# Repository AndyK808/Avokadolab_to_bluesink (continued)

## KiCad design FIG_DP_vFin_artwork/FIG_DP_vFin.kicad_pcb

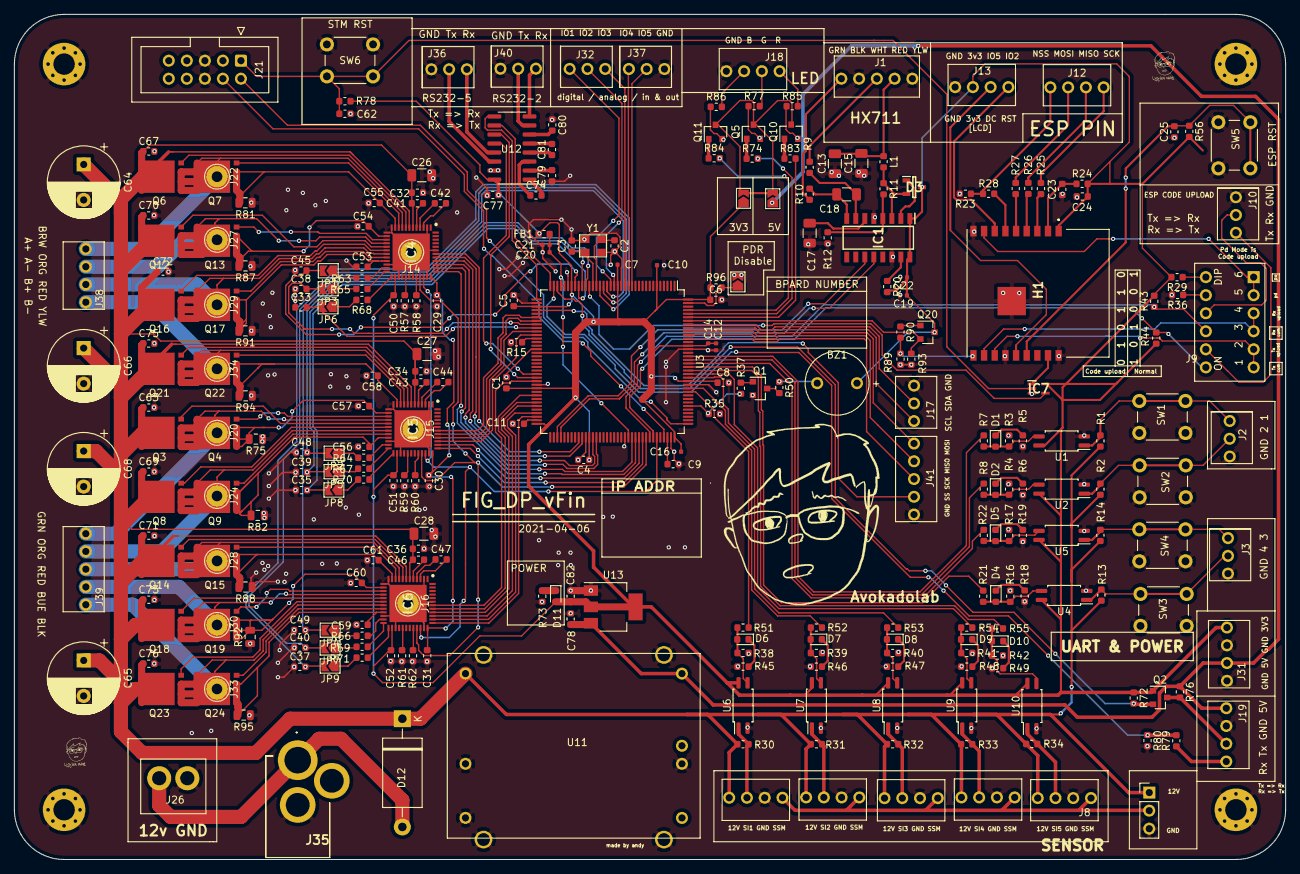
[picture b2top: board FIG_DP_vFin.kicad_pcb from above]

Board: 2 copper layers, 179.0 x 119.0 mm, 301 parts (0 on the bottom side), 239 nets.

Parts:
BZ1: Buzzer; BUZZER
C1, C4: 4.7uF; C_0603_1608Metric
C2, C3: 4pF; C_0603_1608Metric
C5, C6, C8, C23, C24, C32, C34, C36, C50, C51, C52, C74, C77, C79, C80, C81: 0.1uF; C_0603_1608Metric
C7, C10, C12, C14, C16, C19, C20, C22: 0.1uF; C_0402_1005Metric
C9, C11: 2.2uF; C_0603_1608Metric
C13, C18: 0.1uF; C_1206_3216Metric
C15, C17, C26, C27, C28: 10uF; C_1206_3216Metric
C21: 1uF; C_0402_1005Metric
C25, C53, C54, C55, C56, C57, C58, C59, C60, C61, C62: 1nF; C_0603_1608Metric
C29, C30, C31, C41, C43, C46, C63, C67, C69, C70, C71, C72, C73, C75, C76, C78, C82: 1uF; C_0603_1608Metric
C33, C35, C37, C38, C39, C40, C45, C48, C49: 2.2nF; C_0603_1608Metric
C42, C44, C47: 47nF; C_0603_1608Metric
C64, C65, C66, C68: 330uF; CP_Radial_D10.0mm_P5.00mm
D1, D2, D4, D5, D6, D7, D8, D9, D10, D11: LED; LED_0603_1608Metric
D3: MMBT4403; SOT95P240X110-3N
D12: DIODE; D_DO-27_P15.24mm_Horizontal
FB1: Ferrite_Bead; L_0603_1608Metric
H1: ESP-WROOM-02D; ESPWROOM02D
H2, H3, H4, H5: MountingHole_Pad; MountingHole_3mm_Pad_Via
IC1: HX711; SOIC127P600X160-16N
IC4, IC5, IC6: DRV8323RHRGZR; QFN50P700X700X100-49N-D
IC7: SN74AUP1T87DCKR; SOT65P210X110-5N
J1, J39, J41: Conn_01x05; 5045-05
J2, J3, J10, J17, J32, J36, J37, J40: Conn_01x03; 5045-03
J4, J5, J6, J7, J8, J12, J13, J18, J19, J31, J38: Conn_01x04; 5045-04
J9: Conn_02x06_Top_Bottom; slid_SW_SPST_6_array
J11: Conn_01x03; PinHeader_1x03_P2.54mm_Vertical
J14, J15, J16, J20, J22, J24, J27, J28, J29, J30, J33, J34: Conn_01x01; TestPoint_THTPad_D3.0mm_Drill1.5mm
J21: Conn_02x05_Odd_Even; IDC-Header_2x05_P2.54mm_Vertical
J26: Conn_01x02; LWB1143-02
J35: DCJ200-10-A-K1-K; DCJ20010AK1K
JP1, JP2, JP3, JP4, JP5, JP6, JP7, JP8, JP9, JP10, JP11, JP12: SolderJumper_2_Open; SolderJumper-2_P1.3mm_Open_TrianglePad1.0x1.5mm
L1: AIML-0603-3R3K-T(3.3uH); L_0603_1608Metric
NT1, NT2, NT3: Net-Tie_2; NET_TIE_0_25
Q1, Q2, Q5, Q10, Q11, Q20: BSS138; SOT-23
Q3, Q4, Q6, Q7, Q8, Q9, Q12, Q13, Q14, Q15, Q16, Q17, Q18, Q19, Q21, Q22, Q23, Q24: CSD18537NQ5A
R1, R2, R13, R14, R30, R31, R32, R33, R34: 4.7k; R_0603_1608Metric
R3, R4, R15, R16, R17, R20, R23, R24, R29, R35, R36, R38, R39, R40, R41, R42, R43, R44, R56, R72, R76, R78, R89, R93, R96: 10k; R_0603_1608Metric
R5, R6, R18, R19, R45, R46, R47, R48, R49: 1k; R_0603_1608Metric
R7, R8, R9, R10, R21, R22, R37, R51, R52, R53, R54, R55, R74, R83, R84, R90: 100; R_0603_1608Metric
R11: 20k; R_0603_1608Metric
R12: 8k2; R_0603_1608Metric
R25, R26, R27, R28: 120; R_0603_1608Metric
R50: 47; R_0603_1608Metric
R57, R59, R61: 47K; R_0603_1608Metric
R58, R60, R62, R86: 0; R_0603_1608Metric
R63, R64, R65, R66, R67, R68, R69, R70, R71: 56; R_0603_1608Metric
R73: 220; R_0603_1608Metric
R75, R81, R82, R87, R88, R91, R92, R94, R95: 0.01; C_0805_2012Metric
R77: 15; R_0603_1608Metric
R79: 2k2; R_0603_1608Metric
R80: 3k3; R_0603_1608Metric
R85: 75; R_0603_1608Metric
SW1, SW2, SW3, SW4, SW5, SW6: SW_Push; SW_PUSH_6mm_H5mm
U1, U2, U4, U5, U6, U7, U8, U9, U10: TCMT1102; SOP-4_4.4x2.6mm_P1.27mm
U3: STM32F446ZETx; LQFP-144_20x20mm_P0.5mm
U11: SPS10-12-5
U12: MAX3232; SOIC-16_3.9x9.9mm_P1.27mm
U13: TLV1117-33; SOT-223-3_TabPin2
Y1: 16MHz; ABM8

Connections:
/3V3: BZ1.1, C1.1, C4.1, C5.1, C6.1, C7.1, C8.1, C10.1, C12.1, C14.1, C16.1, C19.1, C22.1, C24.2, C50.1, C51.1, C52.1, C77.2, C82.1, D3.3, D11.2, FB1.1, H1.1, IC1.1, IC1.16, IC4.26, IC5.26, IC6.26, IC7.5, J13.3, J31.4, JP10.1, Q2.1, Q20.3, R20.2, R24.2, R29.2, R43.2, R44.2, R56.2, R72.1, R78.1, R96.1, U1.4, U2.4, U3.6, U3.17, U3.30, U3.39, U3.52, U3.62, U3.72, U3.84, U3.108, U3.121, U3.131, U3.144, U4.4, U5.4, U6.4, U7.4, U8.4, U9.4, U10.4, U12.16, U13.2
/5V: C78.1, J19.4, J31.2, JP11.1, R76.1, U11.7, U13.3
/12V: C26.1, C27.1, C28.1, C32.1, C34.1, C36.1, C41.1, C43.1, C46.1, C63.1, C64.1, C65.1, C66.1, C67.1, C68.1, C69.1, C70.1, C71.1, C72.1, C73.1, C75.1, C76.1, D12.1, IC4.6, IC5.6, IC6.6, J4.1, J5.1, J6.1, J7.1, J8.1, J11.1, NT1.2, NT2.2, NT3.2, Q3.1, Q6.1, Q8.1, Q12.1, Q14.1, Q16.1, Q18.1, Q21.1, Q23.1, R1.1, R2.1, R13.1, R14.1, R30.1, R31.1, R32.1, R33.1, R34.1, U11.1
/232_Rx_AND: J40.1, U12.8
/232_Rx_Peri: J36.1, U12.13
/232_Tx_AND: J40.2, U12.7
/232_Tx_Peri: J36.2, U12.14
/AVDD: C20.1, C21.1, FB1.2, U3.32, U3.33, U3.95
/BLUE_LED: J18.3, R86.2
/BOOT0_ESP: H1.10, R89.1, R90.2
/BOOT0_STM: Q20.2, R93.1, U3.138
/BUZZ: R35.1, R37.2, U3.114
/CAL: IC4.34, IC5.34, IC6.34, U3.103
/DVDD1: C29.1, C30.1, C31.1, IC4.36, IC5.36, IC6.36
/EN_GATE: IC4.33, IC5.33, IC6.33, U3.100
/ESP_BOOT_MODE: H1.8, J9.7, J9.8
/ESP_Rx: H1.11, J9.9, J9.10
/ESP_SPI_MISO: J12.2, R26.1
/ESP_SPI_MOSI: J12.3, R27.1
/ESP_SPI_NSS: J12.4, R23.1, R28.1
/ESP_SPI_SCK: J12.1, R25.1
/ESP_Tx: H1.12, J9.11, J9.12
/ESP_Upload_Rx: J9.3, J10.2
/ESP_Upload_Tx: J9.5, J10.1
/GHA: IC4.8, Q6.2
/GHB: IC4.17, Q12.2
/GHC: IC4.18, Q16.2
/GHD: IC5.8, Q21.2
/GHE: IC5.17, Q3.2
/GHF: IC5.18, Q8.2
/GHG: IC6.8, Q14.2
/GHH: IC6.17, Q18.2
/GHI: IC6.18, Q23.2
/GLA: IC4.10, Q7.2
/GLB: IC4.15, Q13.2
/GLC: IC4.20, Q17.2
/GLD: IC5.10, Q22.2
/GLE: IC5.15, Q4.2
/GLF: IC5.20, Q9.2
/GLG: IC6.10, Q15.2
/GLH: IC6.15, Q19.2
/GLI: IC6.20, Q24.2
/GREEN_LED: J18.2, R77.2
/GRN: J1.5, R10.1
/HIGH_RXI: J19.1, R79.1
/HIGH_TXO: J19.2, Q2.3, R76.2
/HX711_CLK: IC1.11, U3.75
/HX711_DAT: IC1.12, U3.76
/I1: R7.2, U3.128
/I2: R8.2, U3.127
/I3: R22.2, U3.126
/I4: R21.2, U3.125
/IO2: H1.7, J13.1
/IO5: H1.14, J13.2
/IOIO1: J32.3, U3.19
/IOIO2: J32.2, U3.18
/IOIO3: J32.1, U3.15
/IOIO4: J37.3, U3.14
/IOIO5: J37.2, U3.13
/ISENA: C33.2, JP6.2, U3.45
/ISENB: C38.2, JP3.2, U3.44
/ISENC: C45.2, JP1.2, U3.29
/ISEND: C35.2, JP8.2, U3.28
/ISENE: C39.2, JP5.2, U3.27
/ISENF: C48.2, JP2.2, U3.26
/ISENG: C37.2, JP9.2, U3.22
/ISENH: C40.2, JP7.2, U3.21
/ISENI: C49.2, JP4.2, U3.20
/LED_B: R84.2, U3.141
/LED_G: R74.2, U3.140
/LED_M: JP10.2, JP11.2, Q5.3, Q10.3, Q11.3
/LED_R: R83.2, U3.139
/MISO: J41.4, U3.134
/MOSI: J41.5, U3.135
/RED: C13.2, C15.2, J1.2, L1.1
/RED_LED: J18.1, R85.2
/SCK: J41.3, U3.133
/SCL: J17.1, U3.136
/SDA: J17.2, U3.137
/SHA: IC4.9, J22.1, J38.1, Q6.3, Q7.1
/SHB: IC4.16, J27.1, J38.2, Q12.3, Q13.1
/SHC: IC4.19, J29.1, J38.3, Q16.3, Q17.1
/SHD: IC5.9, J34.1, J38.4, Q21.3, Q22.1
/SHE: IC5.16, J20.1, J39.1, Q3.3, Q4.1
/SHF: IC5.19, J24.1, J39.2, Q8.3, Q9.1
/SHG: IC6.9, J28.1, J39.3, Q14.3, Q15.1
/SHH: IC6.16, J30.1, J39.4, Q18.3, Q19.1
/SHI: IC6.19, J33.1, J39.5, Q23.3, Q24.1
/SI1: R51.2, U3.118
/SI2: R52.2, U3.119
/SI3: R53.2, U3.122
/SI4: R54.2, U3.123
/SI5: R55.2, U3.124
/SPA: C55.2, IC4.11, Q7.3, R81.2
/SPB: C54.2, IC4.14, Q13.3, R87.2
/SPC: C53.2, IC4.21, Q17.3, R91.2
/SPD: C58.2, IC5.11, Q22.3, R94.2
/SPE: C57.2, IC5.14, Q4.3, R75.2
/SPF: C56.2, IC5.21, Q9.3, R82.2
/SPG: C61.2, IC6.11, Q15.3, R88.2
/SPH: C60.2, IC6.14, Q19.3, R92.2
/SPI: C59.2, IC6.21, Q24.3, R95.2
/SPI_SS: J41.2, U3.40
/SSM: J4.4, J5.4, J6.4, J7.4, J8.4, J11.2
/ST2_A+: IC4.37, U3.97
/ST2_A-: IC4.38, U3.96
/ST2_B+: IC4.39, U3.86
/ST2_B-: IC4.40, U3.85
/ST2_C+: IC4.41, U3.82
/ST2_C-: IC4.42, U3.81
/ST2_D+: IC5.37, U3.99
/ST2_D-: IC5.38, U3.98
/ST5_A+: IC5.39, U3.47
/ST5_A-: IC5.40, U3.46
/ST5_B+: IC5.41, U3.43
/ST5_B-: IC5.42, U3.42
/ST5_C+: IC6.37, U3.70
/ST5_C-: IC6.38, U3.69
/ST5_D+: IC6.39, U3.67
/ST5_D-: IC6.40, U3.66
/ST5_E+: IC6.41, U3.64
/ST5_E-: IC6.42, U3.60
/STM_RST: IC7.4, U3.25
/STM_RST1: H1.17, IC7.1
/STM_RST2: C62.1, IC7.2, J21.1, R78.2, SW6.2
/STM_USART1_Rx: J9.6, R44.1, U3.102
/STM_USART1_Tx: J9.4, R43.1, U3.101
/SW1: J2.3, R1.2, SW1.2, U1.1
/SW2: J2.2, R2.2, SW2.2, U2.1
/SW3: J3.3, R14.2, SW4.2, U5.1
/SW4: J3.2, R13.2, SW3.2, U4.1
/SWCLK: J21.2, U3.109
/SWDIO: J21.4, U3.105
/UART4_RX: R79.2, R80.1, U3.35
/UART4_TX: Q2.2, R72.2, U3.34
/UART5_Rx: U3.58, U12.12
/UART5_Tx: U3.59, U12.11
/USART2_Rx: U3.37, U12.9
/USART2_Tx: U3.36, U12.10
/WHT: J1.3, R9.1
/~12V: D12.2, J26.2, J35.1
GND: C1.2, C2.2, C3.1, C4.2, C5.2, C6.2, C7.2, C8.2, C9.2, C10.2, C11.2, C12.2, C13.1, C14.2, C15.1, C16.2, C17.1, C19.2, C20.2, C21.2, C22.2, C23.1, C24.1, C25.1, C26.2, C27.2, C28.2, C29.2, C30.2, C31.2, C32.2, C33.1, C34.2, C35.1, C36.2, C37.1, C38.1, C39.1, C40.1, C45.1, C48.1, C49.1, C50.2, C51.2, C52.2, C53.1, C54.1, C55.1, C56.1, C57.1, C58.1, C59.1, C60.1, C61.1, C62.2, C63.2, C64.2, C65.2, C66.2, C67.2, C68.2, C69.2, C70.2, C71.2, C72.2, C73.2, C75.2, C76.2, C77.1, C78.2, C79.1, C80.1, C82.2, H1.9, H1.13, H1.18, H1.19, H2.1, H3.1, H4.1, H5.1, IC1.5, IC1.14, IC4.2, IC4.12, IC4.13, IC4.22, IC4.27, IC4.35, IC4.43, IC4.49, IC5.2, IC5.12, IC5.13, IC5.22, IC5.27, IC5.35, IC5.43, IC5.49, IC6.2, IC6.12, IC6.13, IC6.22, IC6.27, IC6.35, IC6.43, IC6.49, IC7.3, J1.1, J1.4, J2.1, J3.1, J4.3, J5.3, J6.3, J7.3, J8.3, J10.3, J11.3, J13.4, J14.1, J15.1, J16.1, J17.3, J18.4, J19.3, J21.5, J21.6, J26.1, J31.1, J31.3, J35.2, J36.3, J37.1, J40.3, J41.1, JP12.2, Q1.2, R3.2, R4.2, R5.2, R6.2, R12.2, R15.2, R16.2, R17.2, R18.2, R19.2, R23.2, R35.2, R36.2, R38.2, R39.2, R40.2, R41.2, R42.2, R45.2, R46.2, R47.2, R48.2, R49.2, R57.2, R58.2, R59.2, R60.2, R61.2, R62.2, R73.2, R75.1, R80.2, R81.1, R82.1, R87.1, R88.1, R89.2, R91.1, R92.1, R93.2, R94.1, R95.1, SW1.1, SW2.1, SW3.1, SW4.1, SW5.1, SW6.1, U1.2, U2.2, U3.16, U3.31, U3.38, U3.51, U3.61, U3.83, U3.94, U3.107, U3.120, U3.130, U4.2, U5.2, U6.2, U7.2, U8.2, U9.2, U10.2, U11.2, U11.3, U11.5, U11.SH, U12.15, U13.1, Y1.2, Y1.4
unnamed: BZ1.2, R50.1
unnamed: C2.1, U3.23, Y1.1
unnamed: C3.2, U3.24, Y1.3
unnamed: C9.1, U3.106
unnamed: C11.1, U3.71
unnamed: C17.2, IC1.6
unnamed: C18.1, IC1.8, R10.2
unnamed: C18.2, IC1.7, R9.2
unnamed: C23.2, H1.2, R24.1
unnamed: C25.2, H1.15, R56.1, SW5.2
unnamed: C41.2, IC4.5
unnamed: C42.1, IC4.4
unnamed: C42.2, IC4.3
unnamed: C43.2, IC5.5
unnamed: C44.1, IC5.4
unnamed: C44.2, IC5.3
unnamed: C46.2, IC6.5
unnamed: C47.1, IC6.4
unnamed: C47.2, IC6.3
unnamed: C74.1, U12.3
unnamed: C74.2, U12.1
unnamed: C79.2, U12.2
unnamed: C80.2, U12.6
unnamed: C81.1, U12.4
unnamed: C81.2, U12.5
unnamed: D1.1, R5.1
unnamed: D1.2, R3.1, R7.1, U1.3
unnamed: D2.1, R6.1
unnamed: D2.2, R4.1, R8.1, U2.3
unnamed: D3.1, IC1.2
unnamed: D3.2, IC1.3, L1.2, R11.1
unnamed: D4.1, R18.1
unnamed: D4.2, R16.1, R21.1, U4.3
unnamed: D5.1, R19.1
unnamed: D5.2, R17.1, R22.1, U5.3
unnamed: D6.1, R45.1
unnamed: D6.2, R38.1, R51.1, U6.3
unnamed: D7.1, R46.1
unnamed: D7.2, R39.1, R52.1, U7.3
unnamed: D8.1, R47.1
unnamed: D8.2, R40.1, R53.1, U8.3
unnamed: D9.1, R48.1
unnamed: D9.2, R41.1, R54.1, U9.3
unnamed: D10.1, R49.1
unnamed: D10.2, R42.1, R55.1, U10.3
unnamed: D11.1, R73.1
unnamed: H1.3, R25.2
unnamed: H1.4, R26.2
unnamed: H1.5, R27.2
unnamed: H1.6, R28.2
unnamed: IC1.4, R11.2, R12.1
unnamed: IC1.15, R20.1
unnamed: IC4.7, NT1.1
unnamed: IC4.23, R63.1
unnamed: IC4.24, R65.1
unnamed: IC4.25, R68.1
unnamed: IC4.29, R57.1
unnamed: IC4.32, R58.1
unnamed: IC5.7, NT2.1
unnamed: IC5.23, R64.1
unnamed: IC5.24, R67.1
unnamed: IC5.25, R70.1
unnamed: IC5.29, R59.1
unnamed: IC5.32, R60.1
unnamed: IC6.7, NT3.1
unnamed: IC6.23, R66.1
unnamed: IC6.24, R69.1
unnamed: IC6.25, R71.1
unnamed: IC6.29, R61.1
unnamed: IC6.32, R62.1
unnamed: J4.2, R30.2, U6.1
unnamed: J5.2, R31.2, U7.1
unnamed: J6.2, R32.2, U8.1
unnamed: J7.2, R33.2, U9.1
unnamed: J8.2, R34.2, U10.1
unnamed: J9.1, R29.1
unnamed: J9.2, R36.1
unnamed: JP1.1, R63.2
unnamed: JP2.1, R64.2
unnamed: JP3.1, R65.2
unnamed: JP4.1, R66.2
unnamed: JP5.1, R67.2
unnamed: JP6.1, R68.2
unnamed: JP7.1, R69.2
unnamed: JP8.1, R70.2
unnamed: JP9.1, R71.2
unnamed: JP12.1, R96.2, U3.143
unnamed: Q1.1, R37.1
unnamed: Q1.3, R50.2
unnamed: Q5.1, R74.1
unnamed: Q5.2, R77.1
unnamed: Q10.1, R83.1
unnamed: Q10.2, R85.1
unnamed: Q11.1, R84.1
unnamed: Q11.2, R86.1
unnamed: Q20.1, R90.1
unnamed: R15.1, U3.48

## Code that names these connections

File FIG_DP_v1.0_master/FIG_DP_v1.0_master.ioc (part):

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Mcu.Name=STM32F446V(C-E)Tx
Mcu.Package=LQFP100
Mcu.UserName=STM32F446VCTx
PA0-WKUP.Mode=Asynchronous
PA0-WKUP.Signal=UART4_TX
PA1.GPIOParameters=GPIO_Label
PA1.GPIO_Label=Peri(uart)
PA1.Mode=Asynchronous
PA1.Signal=UART4_RX
PA2.Mode=Asynchronous
PA2.Signal=USART2_TX
PA3.GPIOParameters=GPIO_Label
PA3.GPIO_Label=Peri(RS232)
PA3.Mode=Asynchronous
PA3.Signal=USART2_RX
PA5.Signal=S_TIM2_CH1_ETR
PA6.Signal=S_TIM3_CH1
PA7.Signal=S_TIM3_CH2
PA8.GPIOParameters=GPIO_Label
PA8.GPIO_Label=Motor Enable
PA8.Signal=GPIO_Output
PB0.Signal=S_TIM3_CH3
PB1.Signal=S_TIM3_CH4
PB10.Signal=S_TIM2_CH3
PB14.GPIOParameters=GPIO_Label
PB14.GPIO_Label=Hx711
PB14.Signal=GPIO_Output
PB15.Signal=GPIO_Input
PB3.Signal=GPIO_Input
PB4.Signal=GPIO_Input
PB5.Signal=GPIO_Input
PB6.Signal=GPIO_Input
PC11.GPIOParameters=PinState,GPIO_PuPd,GPIO_Label
PC11.GPIO_Label=Buzzer
PC11.GPIO_PuPd=GPIO_PULLDOWN
PC11.PinState=GPIO_PIN_RESET
PC11.Signal=GPIO_Output
PC6.Signal=S_TIM8_CH1
PC7.Signal=S_TIM8_CH2
PC8.Signal=S_TIM8_CH3
PC9.Signal=S_TIM8_CH4
PD0.Signal=GPIO_Input
PD1.Signal=GPIO_Input
PD12.Signal=S_TIM4_CH1
PD13.Signal=S_TIM4_CH2
PD14.Signal=S_TIM4_CH3
PD15.Signal=S_TIM4_CH4
PD2.Signal=GPIO_Input
PD3.Signal=GPIO_Input
PD4.Signal=GPIO_Input
PD5.Signal=GPIO_Input
PD6.Signal=GPIO_Input
PD7.Signal=GPIO_Input
PE11.Signal=S_TIM1_CH2
PE13.Signal=S_TIM1_CH3
PE14.Signal=S_TIM1_CH4
PE9.Signal=S_TIM1_CH1
PH0-OSC_IN.Mode=HSE-External-Oscillator
PH0-OSC_IN.Signal=RCC_OSC_IN
PH1-OSC_OUT.Mode=HSE-External-Oscillator
PH1-OSC_OUT.Signal=RCC_OSC_OUT
RCC.HSE_VALUE=16000000
RCC.SYSCLKFreq_VALUE=180000000
RCC.SYSCLKSource=RCC_SYSCLKSOURCE_PLLCLK
board=custom

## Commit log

2021-04-19 init
